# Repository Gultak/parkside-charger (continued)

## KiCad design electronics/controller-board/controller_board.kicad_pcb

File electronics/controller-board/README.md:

# Controller board (KiCad 9)

The controller board is the hub of the charger. It holds the **xyzroe ESP32-C6 D1** in female Dupont headers,
switches the 24 V for the slot chains, and runs one I²C channel to each of up to **16 slots**.
**112 × 64 mm (rev C), 4 layers** (In1/In2 = GND), all parts on one side.

| Top (parts side) with silkscreen | Bottom copper |
|---|---|
|  |  |
| **Inner layer 1** (In1) | **Inner layer 2** (In2) |
|  |  |

**Why 4 layers?** This board has no switching converter (the 5 V regulator is a module), so
2 layers would do. It uses 4 because the 32 slot I²C lines fan out from two TSSOP muxes on a
compact board: with GND planes inside, they route on the outer layers without stitching a
ground pour around them, and the 24 V band stays separate. The extra cost is small.

| File | |
|---|---|
| `controller_board.kicad_pro / .kicad_sch / .kicad_pcb` | KiCad 9 project |
| `pcl.kicad_sym`, `pcl.pretty/` | Custom symbols and the ESP32-C6 D1 socket footprint (holes from the module's own drill file) |
| `controller_board_schematic.pdf` | Schematic |
| `fab/controller_board_gerbers.zip`, `fab/*_bom.csv`, `fab/*_cpl.csv` | Gerbers, BOM and pick-and-place positions |
| `drc_report.txt` | KiCad DRC result |
| `tools/design.py`, `tools/layout.py` | Source: **edit these, then run `/usr/bin/python3 tools/build.py`** |

## Layout and connectors

| Where | What |
|---|---|
| Top edge, centre | **ESP32-C6 D1** in 2 × 1×8 female Dupont headers (holes 1.0 mm, rows 22.86 mm apart). The USB-C faces the edge for flashing. The antenna points into the board, and the board has **no copper on any layer** below it |
| Beside the module | Left: **J8** power LED (2-pin), the enclosure NTC **RT1** (10 kΩ, read on IO5), the I²C pull-ups and the buzzer. Right: **J6** expansion (3V3 GND IO5 IO6 IO7 TX RX, vertical), the voltage dividers, **J7** 4-pin PC fan header with its PWM driver, and **J9** (JST PH 2-pin), the +12 V input from the PSU's fan connector CN101, wired 1:1 |
| Left / right edge | **J101–J108**: slots 1–8. **J109–J116**: slots 9–16, at a 7 mm pitch. All are JST-XH 4-pin, `5V GND SDA SCL`, the same order as the slot board's J2, so cables are wired 1:1 |
| Bottom edge | **J1** 24 V from the PSU (JST B6P-VH, pins 1-3 +V, 4-6 −V, as on the LOP-300 output) → **10 A mini blade fuse** → TVS → AOD4185 bus switch (soft start, GPIO19) → **J2 OUT A** and **J3 OUT B** (vertical XT30 females, two slot daisy chains). Above OUT B: the **TSR 1-2450** 5 V regulator and a 0.5 A PTC for the slot 5 V rail |
| Between module and connectors | 2 × TCA9548A (0x70 for slots 1–8, 0x71 for 9–16), rotated so each pin row faces its connectors, plus 8 × 4.7 kΩ pull-up arrays to 5V_SLOT |
| Corners | 4 × M3 mounting holes |

The 24 V input, the switched 24 V, and the PSU-to-switch section are pours on both outer layers
(fuse limit 10 A).

## Assembly notes

- **ESP socket:** solder two 1×8 female Dupont headers (2.54 mm pin sockets) into the U2
  position. Solder male pin headers to the ESP32-C6 D1 (it usually ships with them). Plug the
  module in with the USB towards the board edge.
- The silkscreen next to the socket holes shows the module's pin names, so you can check the
  orientation before plugging it in.
- **TSR 1-2450:** fit it upright (SIP-3). The footprint also takes a RECOM R-78E5.0-1.0.

## Before ordering: check these

1. **Review the routing in KiCad.** The custom router routed this board automatically, and
   the KiCad DRC shows **no errors or unconnected items**. What's left: silkscreen cosmetics, one
   0.3 mm dangling +3V3 stub (you can delete it), and `lib_footprint_issues`, which only appears
   because the generator runs without the global library table.
2. Standard 2.54 mm female headers fit the 1.0 mm holes; no special parts needed.
3. **Power connectors:** J1 (VH, from the PSU through the partition notch) and the vertical XT30
   females J2/J3 take their plugs from above; the chain cables then run along the cable channel
   to the side-wall notches. The box is 48 mm tall inside to leave room for the XT30 plugs.

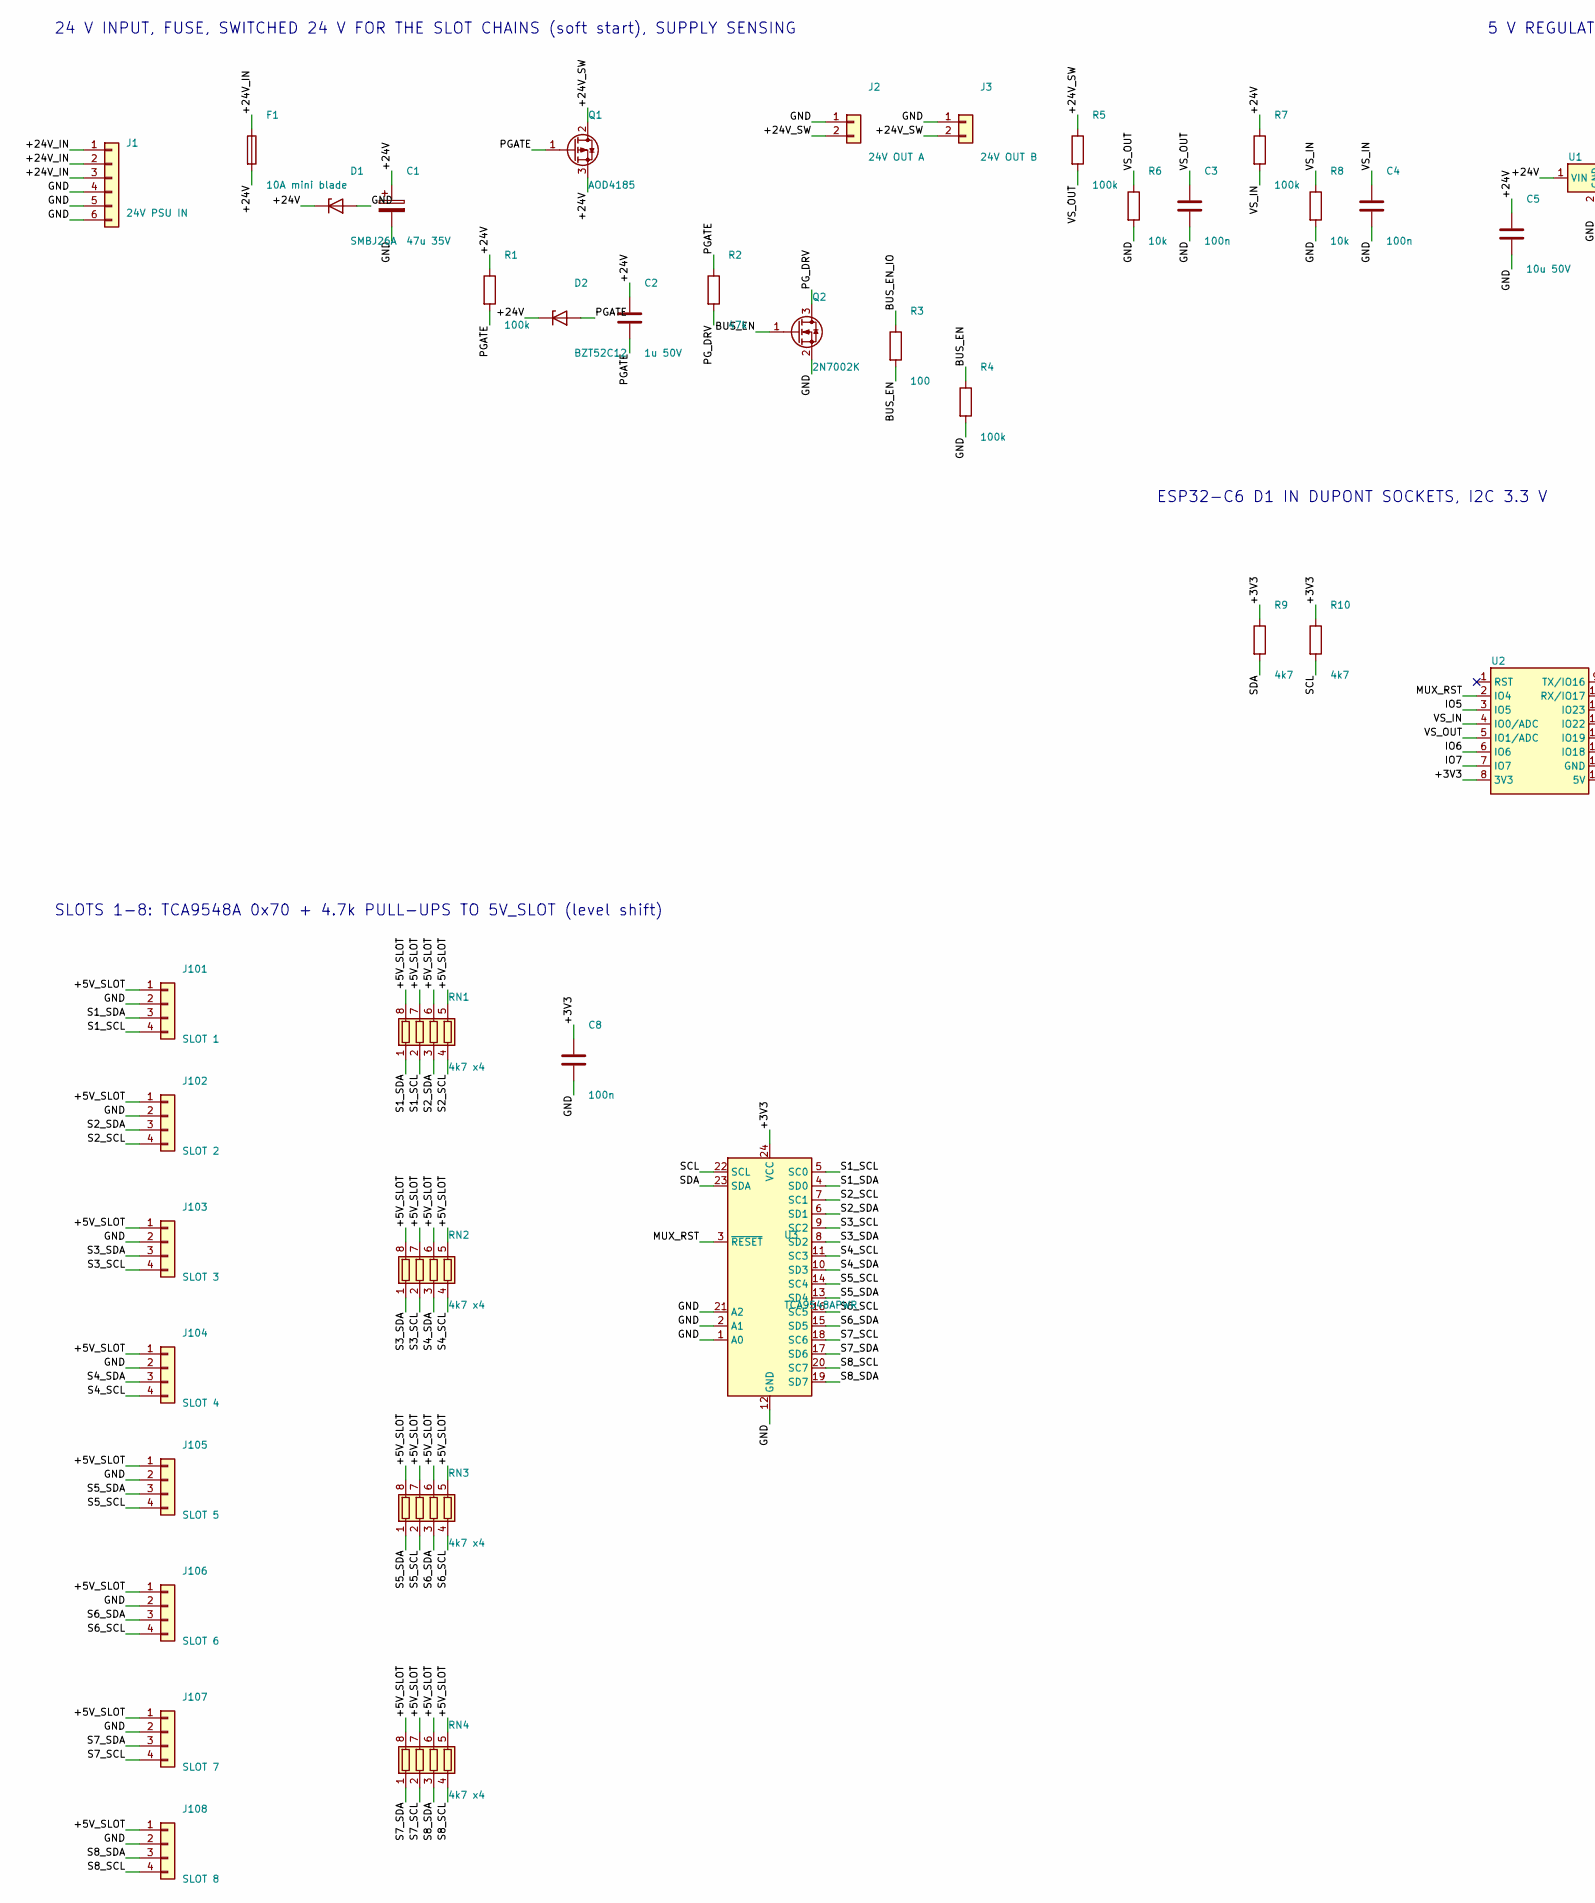
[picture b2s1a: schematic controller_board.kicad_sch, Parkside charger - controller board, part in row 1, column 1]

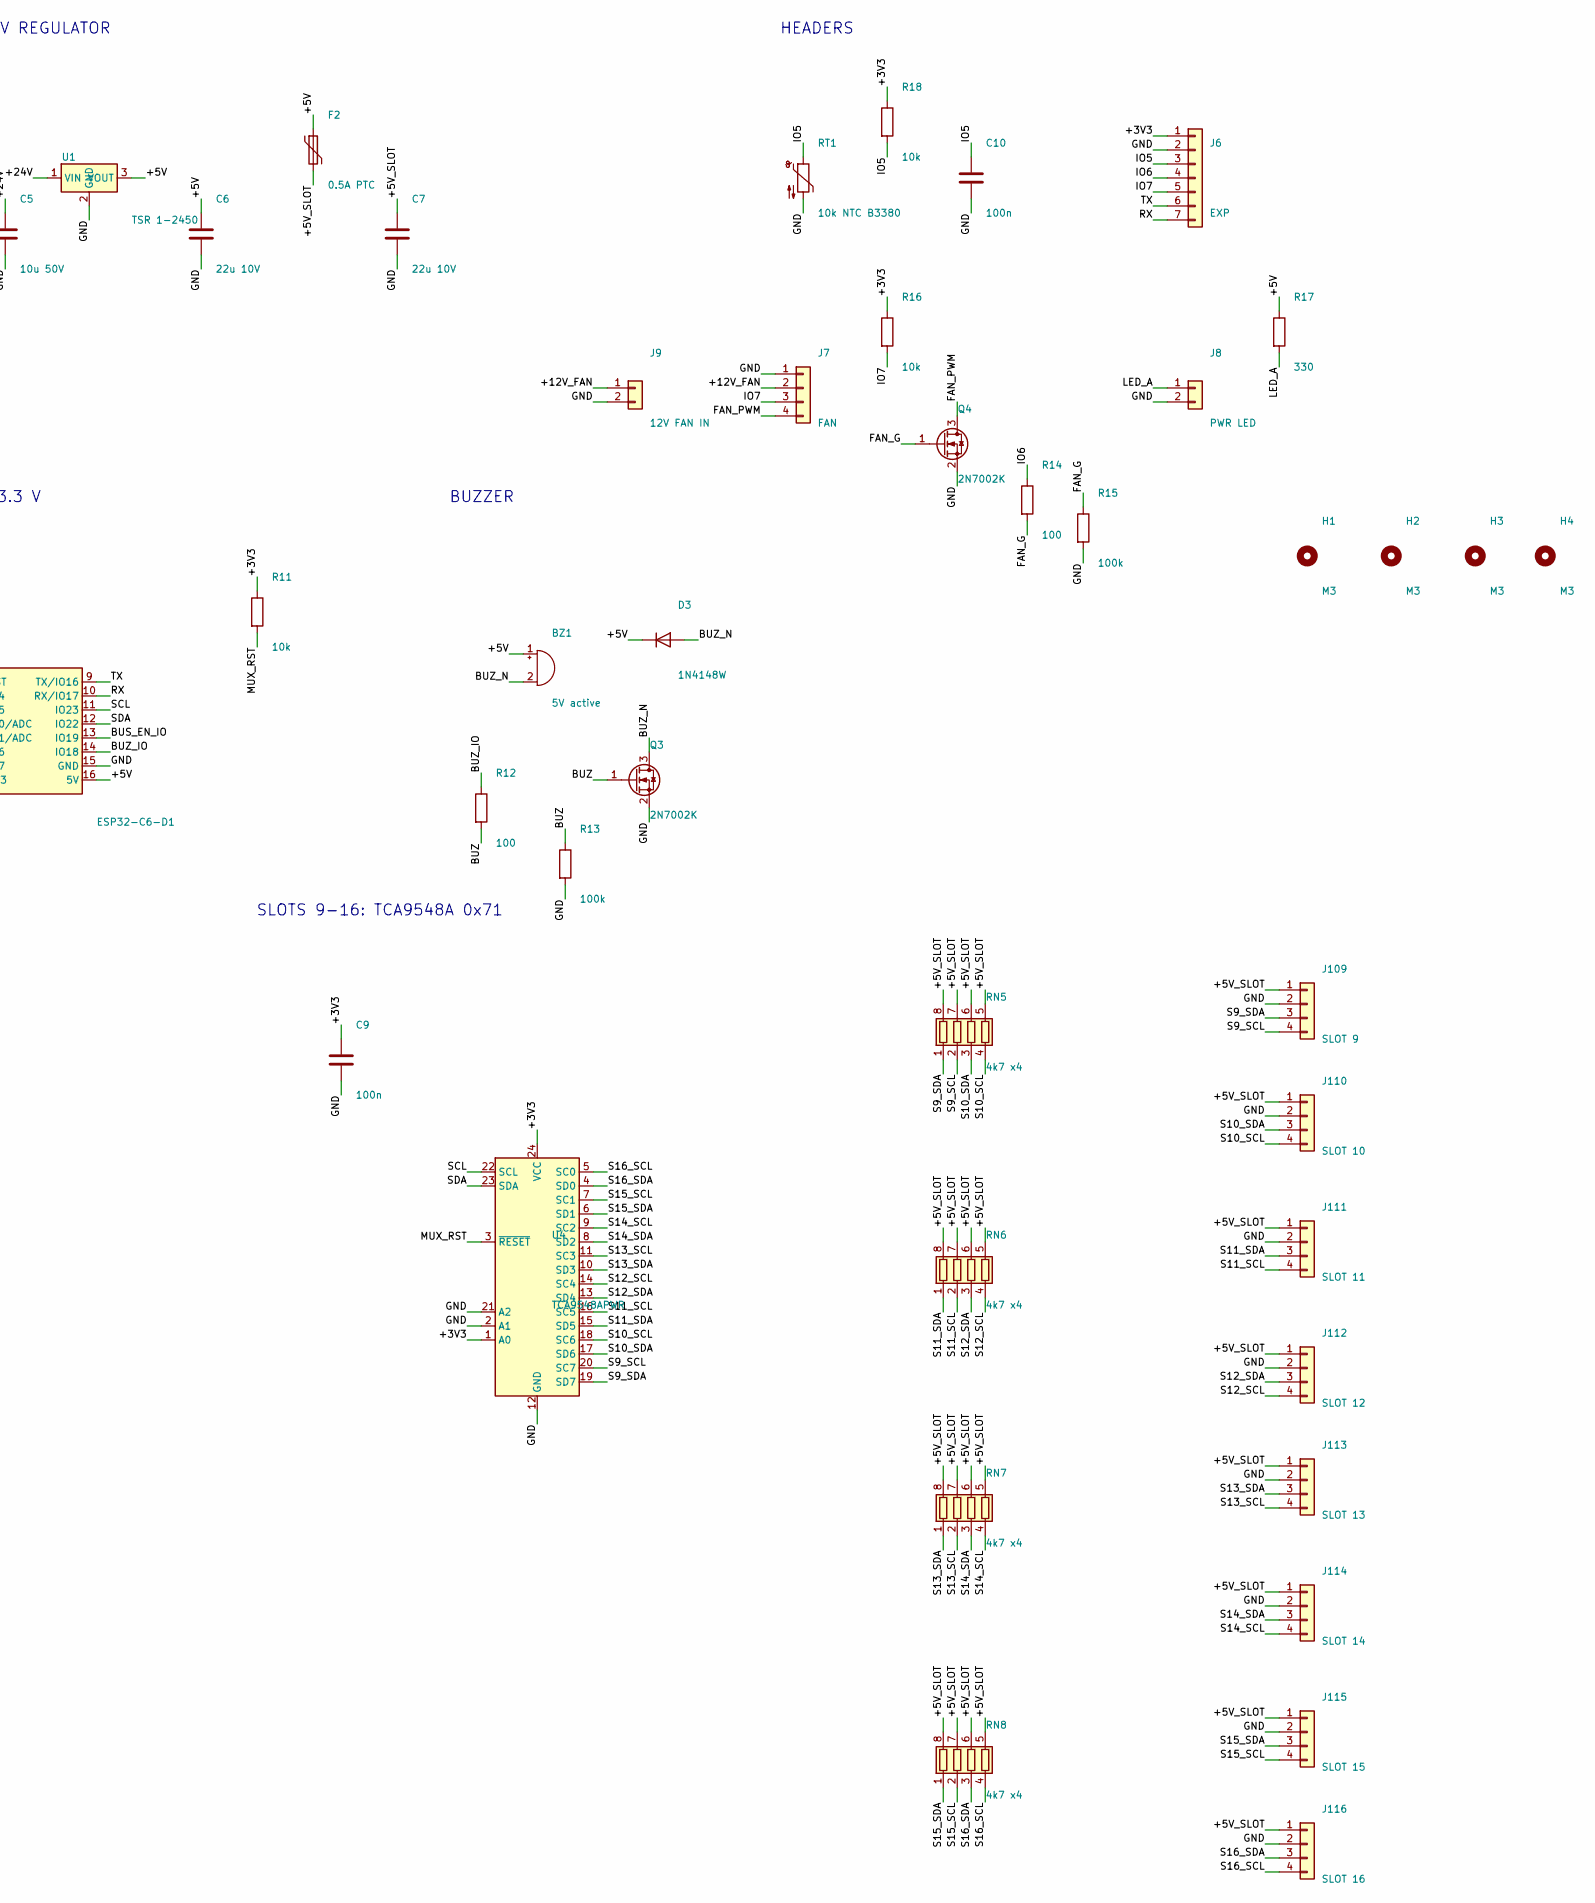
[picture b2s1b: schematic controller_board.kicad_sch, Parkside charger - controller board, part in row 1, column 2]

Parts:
BZ1: 5V active; Buzzer_12x9.5RM7.6; MPN 12 mm active buzzer 5 V
C1: 47u 35V; CP_Elec_6.3x7.7
C2: 1u 50V; C_1206_3216Metric; MPN soft start: slow turn-on into the slot 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
C3, C4, C8, C9: 100n; C_0603_1608Metric
C5: 10u 50V; C_1206_3216Metric
C6, C7: 22u 10V; C_1206_3216Metric
C10: 100n; C_0603_1608Metric; MPN ADC filter
D1: SMBJ26A; D_SMB; MPN TVS 26 V
D2: BZT52C12; D_SOD-123; MPN Vgs clamp 12 V
D3: 1N4148W; D_SOD-123
F1: 10A mini blade; Fuseholder_Blade_Mini_Keystone_3568; MPN Keystone 3568 holder + 10 A mini blade 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
F2: 0.5A PTC; Fuse_1206_3216Metric; MPN Bourns MF-NSMF050 - slot 5 V rail
H1, H2, H3, H4: M3; MountingHole_3.2mm_M3
J1: 24V PSU IN; JST_VH_B6P-VH_1x06_P3.96mm_Vertical; MPN JST B6P-VH (pins 1-3 +V, 4-6 -V, as on 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
J2: 24V OUT A; AMASS_XT30UPB-F_1x02_P5.0mm_Vertical; MPN Amass XT30UPB-F: to the first slot of c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
J3: 24V OUT B; AMASS_XT30UPB-F_1x02_P5.0mm_Vertical; MPN Amass XT30UPB-F: to the first slot of c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
J6: EXP; PinHeader_1x07_P2.54mm_Vertical; MPN spare GPIO (IO5 is the enclosure NTC, I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
J7: FAN; FanPinHeader_1x04_P2.54mm_Vertical; MPN 4-pin PC fan header (Molex 47053-1000 o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
J8: PWR LED; PinHeader_1x02_P2.54mm_Vertical; MPN 2-pin header: power LED (Lumex SSI-LXMP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
J9: 12V FAN IN; JST_PH_B2B-PH-K_1x02_P2.00mm_Vertical; MPN JST PH 2-pin, same pinout as the PSU's 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
J101: SLOT 1; JST_XH_B4B-XH-A_1x04_P2.50mm_Vertical; MPN slot 1 I2C (JST B4B-XH-A)
J102: SLOT 2; JST_XH_B4B-XH-A_1x04_P2.50mm_Vertical; MPN slot 2 I2C (JST B4B-XH-A)
J103: SLOT 3; JST_XH_B4B-XH-A_1x04_P2.50mm_Vertical; MPN slot 3 I2C (JST B4B-XH-A)
J104: SLOT 4; JST_XH_B4B-XH-A_1x04_P2.50mm_Vertical; MPN slot 4 I2C (JST B4B-XH-A)
J105: SLOT 5; JST_XH_B4B-XH-A_1x04_P2.50mm_Vertical; MPN slot 5 I2C (JST B4B-XH-A)
J106: SLOT 6; JST_XH_B4B-XH-A_1x04_P2.50mm_Vertical; MPN slot 6 I2C (JST B4B-XH-A)
J107: SLOT 7; JST_XH_B4B-XH-A_1x04_P2.50mm_Vertical; MPN slot 7 I2C (JST B4B-XH-A)
J108: SLOT 8; JST_XH_B4B-XH-A_1x04_P2.50mm_Vertical; MPN slot 8 I2C (JST B4B-XH-A)
J109: SLOT 9; JST_XH_B4B-XH-A_1x04_P2.50mm_Vertical; MPN slot 9 I2C (JST B4B-XH-A)
J110: SLOT 10; JST_XH_B4B-XH-A_1x04_P2.50mm_Vertical; MPN slot 10 I2C (JST B4B-XH-A)
J111: SLOT 11; JST_XH_B4B-XH-A_1x04_P2.50mm_Vertical; MPN slot 11 I2C (JST B4B-XH-A)
J112: SLOT 12; JST_XH_B4B-XH-A_1x04_P2.50mm_Vertical; MPN slot 12 I2C (JST B4B-XH-A)
J113: SLOT 13; JST_XH_B4B-XH-A_1x04_P2.50mm_Vertical; MPN slot 13 I2C (JST B4B-XH-A)
J114: SLOT 14; JST_XH_B4B-XH-A_1x04_P2.50mm_Vertical; MPN slot 14 I2C (JST B4B-XH-A)
J115: SLOT 15; JST_XH_B4B-XH-A_1x04_P2.50mm_Vertical; MPN slot 15 I2C (JST B4B-XH-A)
J116: SLOT 16; JST_XH_B4B-XH-A_1x04_P2.50mm_Vertical; MPN slot 16 I2C (JST B4B-XH-A)
Q1: AOD4185; TO-252-2; MPN P-MOSFET -40 V / -40 A, 15 mOhm (or SQD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
Q2, Q3: 2N7002K; SOT-23
Q4: 2N7002K; SOT-23; MPN fan PWM, open drain
R1: 100k; R_0603_1608Metric; MPN gate pull-up (off)
R2: 47k; R_0603_1608Metric
R3, R12, R14: 100; R_0603_1608Metric
R4: 100k; R_0603_1608Metric; MPN default off while the ESP boots / resets
R5, R7, R13, R15: 100k; R_0603_1608Metric
R6, R8, R11: 10k; R_0603_1608Metric
R9, R10: 4k7; R_0603_1608Metric
R16: 10k; R_0603_1608Metric; MPN fan tach pull-up
R17: 330; R_0603_1608Metric; MPN power LED, about 9 mA
R18: 10k; R_0603_1608Metric; MPN NTC divider
RN1, RN2, RN3, RN4, RN5, RN6, RN7, RN8: 4k7 x4; R_Array_Convex_4x0603; MPN slot bus pull-ups
RT1: 10k NTC B3380; R_0603_1608Metric; MPN Murata NCP18XH103F03RB (10k, B25/50 338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
U1: TSR 1-2450; Converter_DCDC_RECOM_R-78E-0.5_THT; MPN TRACO TSR 1-2450 (6.5-36 V in, 5 V 1 A)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
U2: ESP32-C6-D1; ESP32_C6_D1_Socket; MPN xyzroe ESP32_C6_D1 in 2x 1x8 female Dup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
U3: TCA9548APWR; TSSOP-24_4.4x7.8mm_P0.65mm; MPN TI TCA9548APWR, address 0x70
U4: TCA9548APWR; TSSOP-24_4.4x7.8mm_P0.65mm; MPN TI TCA9548APWR, address 0x71

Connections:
/+3V3: C8.1, C9.1, J6.1, R9.1, R10.1, R11.1, R16.1, R18.1, U2.8 (3V3), U3.24 (VCC), U4.1 (A0), U4.24 (VCC)
/+5V: BZ1.1 (+), C6.1, D3.1 (K), F2.1, R17.1, U1.3 (VOUT), U2.16 (5V)
/+5V_SLOT: C7.1, F2.2, J101.1, J102.1, J103.1, J104.1, J105.1, J106.1, J107.1, J108.1, J109.1, J110.1, J111.1, J112.1, J113.1, J114.1, J115.1, J116.1, RN1.5 (R4.2), RN1.6 (R3.2), RN1.7 (R2.2), RN1.8 (R1.2), RN2.5 (R4.2), RN2.6 (R3.2), RN2.7 (R2.2), RN2.8 (R1.2), RN3.5 (R4.2), RN3.6 (R3.2), RN3.7 (R2.2), RN3.8 (R1.2), RN4.5 (R4.2), RN4.6 (R3.2), RN4.7 (R2.2), RN4.8 (R1.2), RN5.5 (R4.2), RN5.6 (R3.2), RN5.7 (R2.2), RN5.8 (R1.2), RN6.5 (R4.2), RN6.6 (R3.2), RN6.7 (R2.2), RN6.8 (R1.2), RN7.5 (R4.2), RN7.6 (R3.2), RN7.7 (R2.2), RN7.8 (R1.2), RN8.5 (R4.2), RN8.6 (R3.2), RN8.7 (R2.2), RN8.8 (R1.2)
/+12V_FAN: J7.2, J9.1
/+24V: C1.1, C2.1, C5.1, D1.1 (K), D2.1 (K), F1.2, Q1.3 (S), R1.1, R7.1, U1.1 (VIN)
/+24V_IN: F1.1, J1.1, J1.2, J1.3
/+24V_SW: J2.2, J3.2, Q1.2 (D), R5.1
/BUS_EN: Q2.1 (G), R3.2, R4.1
/BUS_EN_IO: R3.1, U2.13 (IO19)
/BUZ: Q3.1 (G), R12.2, R13.1
/BUZ_IO: R12.1, U2.14 (IO18)
/BUZ_N: BZ1.2 (-), D3.2 (A), Q3.3 (D)
/FAN_G: Q4.1 (G), R14.2, R15.1
/FAN_PWM: J7.4, Q4.3 (D)
/GND: C1.2, C3.2, C4.2, C5.2, C6.2, C7.2, C8.2, C9.2, C10.2, D1.2 (A), J1.4, J1.5, J1.6, J2.1, J3.1, J6.2, J7.1, J8.2, J9.2, J101.2, J102.2, J103.2, J104.2, J105.2, J106.2, J107.2, J108.2, J109.2, J110.2, J111.2, J112.2, J113.2, J114.2, J115.2, J116.2, Q2.2 (S), Q3.2 (S), Q4.2 (S), R4.2, R6.2, R8.2, R13.2, R15.2, RT1.2, U1.2 (GND), U2.15 (GND), U3.1 (A0), U3.2 (A1), U3.12 (GND), U3.21 (A2), U4.2 (A1), U4.12 (GND), U4.21 (A2)
/IO5: C10.1, J6.3, R18.2, RT1.1, U2.3 (IO5)
/IO6: J6.4, R14.1, U2.6 (IO6)
/IO7: J6.5, J7.3, R16.2, U2.7 (IO7)
/LED_A: J8.1, R17.2
/MUX_RST: R11.2, U2.2 (IO4), U3.3 (~RESET), U4.3 (~RESET)
/PGATE: C2.2, D2.2 (A), Q1.1 (G), R1.2, R2.1
/PG_DRV: Q2.3 (D), R2.2
/RX: J6.7, U2.10 (RX/IO17)
/S1_SCL: J101.4, RN1.2 (R2.1), U3.5 (SC0)
/S1_SDA: J101.3, RN1.1 (R1.1), U3.4 (SD0)
/S2_SCL: J102.4, RN1.4 (R4.1), U3.7 (SC1)
/S2_SDA: J102.3, RN1.3 (R3.1), U3.6 (SD1)
/S3_SCL: J103.4, RN2.2 (R2.1), U3.9 (SC2)
/S3_SDA: J103.3, RN2.1 (R1.1), U3.8 (SD2)
/S4_SCL: J104.4, RN2.4 (R4.1), U3.11 (SC3)
/S4_SDA: J104.3, RN2.3 (R3.1), U3.10 (SD3)
/S5_SCL: J105.4, RN3.2 (R2.1), U3.14 (SC4)
/S5_SDA: J105.3, RN3.1 (R1.1), U3.13 (SD4)
/S6_SCL: J106.4, RN3.4 (R4.1), U3.16 (SC5)
/S6_SDA: J106.3, RN3.3 (R3.1), U3.15 (SD5)
/S7_SCL: J107.4, RN4.2 (R2.1), U3.18 (SC6)
/S7_SDA: J107.3, RN4.1 (R1.1), U3.17 (SD6)
/S8_SCL: J108.4, RN4.4 (R4.1), U3.20 (SC7)
/S8_SDA: J108.3, RN4.3 (R3.1), U3.19 (SD7)
/S9_SCL: J109.4, RN5.2 (R2.1), U4.20 (SC7)
/S9_SDA: J109.3, RN5.1 (R1.1), U4.19 (SD7)
/S10_SCL: J110.4, RN5.4 (R4.1), U4.18 (SC6)
/S10_SDA: J110.3, RN5.3 (R3.1), U4.17 (SD6)
/S11_SCL: J111.4, RN6.2 (R2.1), U4.16 (SC5)
/S11_SDA: J111.3, RN6.1 (R1.1), U4.15 (SD5)
/S12_SCL: J112.4, RN6.4 (R4.1), U4.14 (SC4)
/S12_SDA: J112.3, RN6.3 (R3.1), U4.13 (SD4)
/S13_SCL: J113.4, RN7.2 (R2.1), U4.11 (SC3)
/S13_SDA: J113.3, RN7.1 (R1.1), U4.10 (SD3)
/S14_SCL: J114.4, RN7.4 (R4.1), U4.9 (SC2)
/S14_SDA: J114.3, RN7.3 (R3.1), U4.8 (SD2)
/S15_SCL: J115.4, RN8.2 (R2.1), U4.7 (SC1)
/S15_SDA: J115.3, RN8.1 (R1.1), U4.6 (SD1)
/S16_SCL: J116.4, RN8.4 (R4.1), U4.5 (SC0)
/S16_SDA: J116.3, RN8.3 (R3.1), U4.4 (SD0)
/SCL: R10.2, U2.11 (IO23), U3.22 (SCL), U4.22 (SCL)
/SDA: R9.2, U2.12 (IO22), U3.23 (SDA), U4.23 (SDA)
/TX: J6.6, U2.9 (TX/IO16)
/VS_IN: C4.1, R7.2, R8.1, U2.4 (IO0/ADC)
/VS_OUT: C3.1, R5.2, R6.1, U2.5 (IO1/ADC)

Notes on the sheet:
24 V INPUT, FUSE, SWITCHED 24 V FOR THE SLOT CHAINS (soft start), SUPPLY SENSING
5 V REGULATOR
HEADERS
ESP32-C6 D1 IN DUPONT SOCKETS, I2C 3.3 V
BUZZER
SLOTS 1-8: TCA9548A 0x70 + 4.7k PULL-UPS TO 5V_SLOT (level shift)
SLOTS 9-16: TCA9548A 0x71

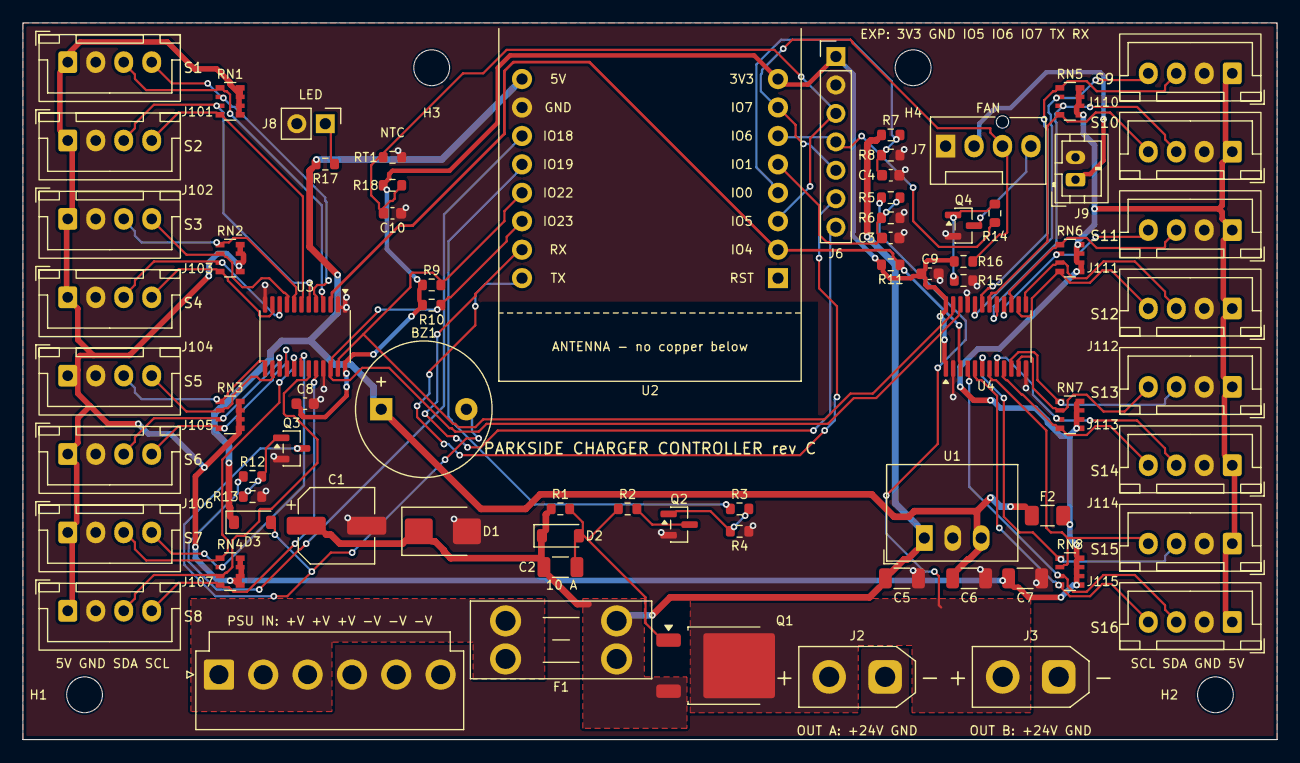
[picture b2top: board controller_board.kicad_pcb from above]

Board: 4 copper layers, 112.0 x 64.0 mm, 78 parts (0 on the bottom side), 60 nets.

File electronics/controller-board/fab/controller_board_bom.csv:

Qty,References,Value,Footprint,MPN / notes
1,BZ1,5V active,Buzzer_12x9.5RM7.6,12 mm active buzzer 5 V
1,C1,47u 35V,CP_Elec_6.3x7.7,
1,C2,1u 50V,C_1206_3216Metric,soft start: slow turn-on into the slot capacitors
4,C3 C4 C8 C9,100n,C_0603_1608Metric,
1,C5,10u 50V,C_1206_3216Metric,
2,C6 C7,22u 10V,C_1206_3216Metric,
1,C10,100n,C_0603_1608Metric,ADC filter
1,D1,SMBJ26A,D_SMB,TVS 26 V
1,D2,BZT52C12,D_SOD-123,Vgs clamp 12 V
1,D3,1N4148W,D_SOD-123,
1,F1,10A mini blade,Fuseholder_Blade_Mini_Keystone_3568,Keystone 3568 holder + 10 A mini blade fuse
1,F2,0.5A PTC,Fuse_1206_3216Metric,Bourns MF-NSMF050 - slot 5 V rail
1,J7,FAN,FanPinHeader_1x04_P2.54mm_Vertical,4-pin PC fan header (Molex 47053-1000 or KF2510-4A)
1,J9,12V FAN IN,JST_PH_B2B-PH-K_1x02_P2.00mm_Vertical,"JST PH 2-pin, same pinout as the PSU's CN101: 1:1 lead"
1,J101,SLOT 1,JST_XH_B4B-XH-A_1x04_P2.50mm_Vertical,slot 1 I2C (JST B4B-XH-A)
1,J102,SLOT 2,JST_XH_B4B-XH-A_1x04_P2.50mm_Vertical,slot 2 I2C (JST B4B-XH-A)
1,J103,SLOT 3,JST_XH_B4B-XH-A_1x04_P2.50mm_Vertical,slot 3 I2C (JST B4B-XH-A)
1,J104,SLOT 4,JST_XH_B4B-XH-A_1x04_P2.50mm_Vertical,slot 4 I2C (JST B4B-XH-A)
1,J105,SLOT 5,JST_XH_B4B-XH-A_1x04_P2.50mm_Vertical,slot 5 I2C (JST B4B-XH-A)
1,J106,SLOT 6,JST_XH_B4B-XH-A_1x04_P2.50mm_Vertical,slot 6 I2C (JST B4B-XH-A)
1,J107,SLOT 7,JST_XH_B4B-XH-A_1x04_P2.50mm_Vertical,slot 7 I2C (JST B4B-XH-A)
1,J108,SLOT 8,JST_XH_B4B-XH-A_1x04_P2.50mm_Vertical,slot 8 I2C (JST B4B-XH-A)
1,J109,SLOT 9,JST_XH_B4B-XH-A_1x04_P2.50mm_Vertical,slot 9 I2C (JST B4B-XH-A)
1,J110,SLOT 10,JST_XH_B4B-XH-A_1x04_P2.50mm_Vertical,slot 10 I2C (JST B4B-XH-A)
1,J111,SLOT 11,JST_XH_B4B-XH-A_1x04_P2.50mm_Vertical,slot 11 I2C (JST B4B-XH-A)
1,J112,SLOT 12,JST_XH_B4B-XH-A_1x04_P2.50mm_Vertical,slot 12 I2C (JST B4B-XH-A)
1,J113,SLOT 13,JST_XH_B4B-XH-A_1x04_P2.50mm_Vertical,slot 13 I2C (JST B4B-XH-A)
1,J114,SLOT 14,JST_XH_B4B-XH-A_1x04_P2.50mm_Vertical,slot 14 I2C (JST B4B-XH-A)
1,J115,SLOT 15,JST_XH_B4B-XH-A_1x04_P2.50mm_Vertical,slot 15 I2C (JST B4B-XH-A)
1,J116,SLOT 16,JST_XH_B4B-XH-A_1x04_P2.50mm_Vertical,slot 16 I2C (JST B4B-XH-A)
1,Q1,AOD4185,TO-252-2,"P-MOSFET -40 V / -40 A, 15 mOhm (or SQD40P06-15L)"
2,Q2 Q3,2N7002K,SOT-23,
1,Q4,2N7002K,SOT-23,"fan PWM, open drain"
1,R1,100k,R_0603_1608Metric,gate pull-up (off)
1,R2,47k,R_0603_1608Metric,
3,R3 R12 R14,100,R_0603_1608Metric,
1,R4,100k,R_0603_1608Metric,default off while the ESP boots / resets
4,R5 R7 R13 R15,100k,R_0603_1608Metric,
3,R6 R8 R11,10k,R_0603_1608Metric,
2,R9 R10,4k7,R_0603_1608Metric,
1,R16,10k,R_0603_1608Metric,fan tach pull-up
1,R17,330,R_0603_1608Metric,"power LED, about 9 mA"
1,R18,10k,R_0603_1608Metric,NTC divider
8,RN1 RN2 RN3 RN4 RN5 RN6 RN7 RN8,4k7 x4,R_Array_Convex_4x0603,slot bus pull-ups
1,RT1,10k NTC B3380,R_0603_1608Metric,"Murata NCP18XH103F03RB (10k, B25/50 3380, 1%): enclosure temperature"
1,U1,TSR 1-2450,Converter_DCDC_RECOM_R-78E-0.5_THT,"TRACO TSR 1-2450 (6.5-36 V in, 5 V 1 A) or RECOM R-78E5.0-1.0"
1,U3,TCA9548APWR,TSSOP-24_4.4x7.8mm_P0.65mm,"TI TCA9548APWR, address 0x70"
1,U4,TCA9548APWR,TSSOP-24_4.4x7.8mm_P0.65mm,"TI TCA9548APWR, address 0x71"

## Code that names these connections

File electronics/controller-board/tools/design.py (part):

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    "C10": ("100n", "Device:C", "Capacitor_SMD:C_0603_1608Metric", {"1": "IO5", "2": "GND"}, "ADC filter"),
    "J6": ("EXP", "Connector_Generic:Conn_01x07", "Connector_PinHeader_2.54mm:PinHeader_1x07_P2.54mm_Vertical",
           {"1": "+3V3", "2": "GND", "3": "IO5", "4": "IO6", "5": "IO7", "6": "TX", "7": "RX"},
           "spare GPIO (IO5 is the enclosure NTC, IO6 / IO7 the fan's PWM / tach)"),
    # --------------------------------------------------- PSU fan + power LED --
    # Standard 4-pin PC fan header (GND, +12V, TACH, PWM). 12 V comes from the PSU's own
    # +12 V aux fan output (CN101, JST PH: 1 +12Vaux, 2 DC COM) through J9, the same PH
    # header, so a 1:1 lead with PH contacts both ends. PWM: open drain, 25 kHz from IO6;
    # tach: open collector from the fan, pulled up to 3.3 V, into IO7.
    "J7": ("FAN", "Connector_Generic:Conn_01x04", "Connector:FanPinHeader_1x04_P2.54mm_Vertical",
           {"1": "GND", "2": "+12V_FAN", "3": "IO7", "4": "FAN_PWM"}, "4-pin PC fan header (Molex 47053-1000 or KF2510-4A)"),
    "J9": ("12V FAN IN", "Connector_Generic:Conn_01x02", "Connector_JST:JST_PH_B2B-PH-K_1x02_P2.00mm_Vertical",
           {"1": "+12V_FAN", "2": "GND"}, "JST PH 2-pin, same pinout as the PSU's CN101: 1:1 lead"),
    "Q4": ("2N7002K", "Transistor_FET:Q_NMOS_GSD", "Package_TO_SOT_SMD:SOT-23",
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    "R15": ("100k", "Device:R", "Resistor_SMD:R_0603_1608Metric", {"1": "FAN_G", "2": "GND"}, ""),
    "R16": ("10k", "Device:R", "Resistor_SMD:R_0603_1608Metric", {"1": "+3V3", "2": "IO7"}, "fan tach pull-up"),
    "J8": ("PWR LED", "Connector_Generic:Conn_01x02", "Connector_PinHeader_2.54mm:PinHeader_1x02_P2.54mm_Vertical",
           {"1": "LED_A", "2": "GND"}, "2-pin header: power LED (Lumex SSI-LXMP059ID), anode on pin 1"),
    "R17": ("330", "Device:R", "Resistor_SMD:R_0603_1608Metric", {"1": "+5V", "2": "LED_A"}, "power LED, about 9 mA"),
}
for i in range(1, 5):
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    "U4": {7: 9, 6: 10, 5: 11, 4: 12, 3: 13, 2: 14, 1: 15, 0: 16},   # 0x71
}
for k, (ref, a0) in enumerate((("U3", "GND"), ("U4", "+3V3"))):   # U3 = 0x70 (slots 1-8), U4 = 0x71 (9-16)
    pins = {"1": a0, "2": "GND", "21": "GND", "3": "MUX_RST", "22": "SCL", "23": "SDA", "24": "+3V3", "12": "GND"}
    for ch in range(8):
        slot = CHANNEL_SLOT[ref][ch]
        pins[_SD[ch]] = f"S{slot}_SDA"
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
